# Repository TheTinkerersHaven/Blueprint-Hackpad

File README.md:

Repo containing the files for my HackPad made for Blueprint by Hack Club & AMD.
---
BOM:
- 1x Seeed Studio XIAO RP2040
- 1x 128x64 0.91" I2C OLED Screen
- 2x ALPS EC11 Rotary Encoders
- 5x Cherry MX-Style Mechanical Key Switches
- 8x M3 threaded inserts (the holes are 4.7mm diameter and 4mm deep)
- 8x M3 Screws
---
Images:

---
NOTE: the case's USB-C hole is taller than usual, to allow the XIAO to be mounted either as SMD or THT.

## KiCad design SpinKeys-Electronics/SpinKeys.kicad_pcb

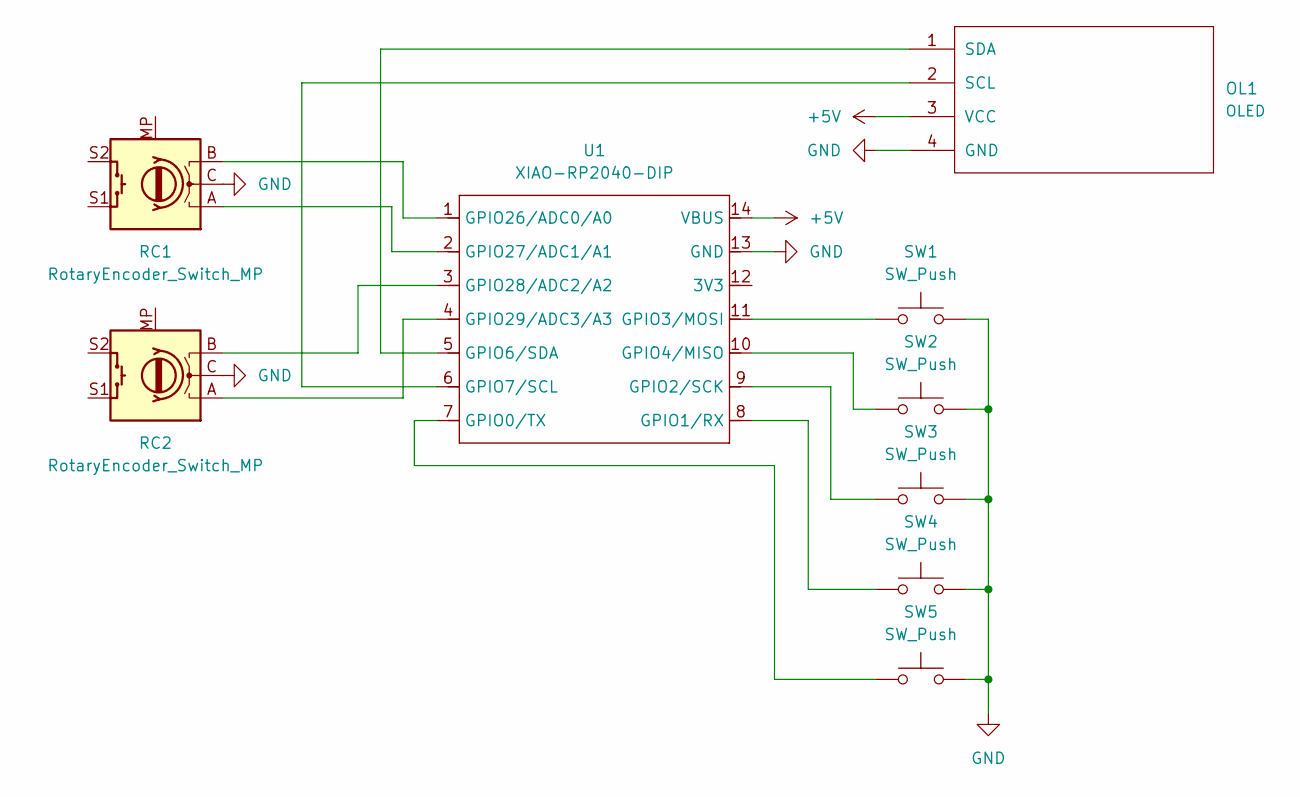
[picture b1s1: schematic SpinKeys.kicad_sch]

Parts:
OL1: OLED; SSD1306-0.91-OLED-4pin-128x32
RC1, RC2: RotaryEncoder_Switch_MP; RotaryEncoder_Alps_EC11E-Switch_Vertical_H20mm_CircularMoun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
SW1, SW2, SW3, SW4, SW5: SW_Push; SW_Cherry_MX_1.00u_PCB
U1: XIAO-RP2040-DIP

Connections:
+5V: OL1.3 (VCC), U1.14 (VBUS)
GND: OL1.4 (GND), RC1.C, RC2.C, SW1.2, SW2.2, SW3.2, SW4.2, SW5.2, U1.13 (GND)
unnamed: OL1.2 (SCL), U1.6 (GPIO7/SCL)
unnamed: OL1.1 (SDA), U1.5 (GPIO6/SDA)
unnamed: SW5.1, U1.7 (GPIO0/TX)
unnamed: SW4.1, U1.8 (GPIO1/RX)
unnamed: SW3.1, U1.9 (GPIO2/SCK)
unnamed: SW1.1, U1.11 (GPIO3/MOSI)
unnamed: SW2.1, U1.10 (GPIO4/MISO)
unnamed: RC1.B, U1.1 (GPIO26/ADC0/A0)
unnamed: RC1.A, U1.2 (GPIO27/ADC1/A1)
unnamed: RC2.B, U1.3 (GPIO28/ADC2/A2)
unnamed: RC2.A, U1.4 (GPIO29/ADC3/A3)

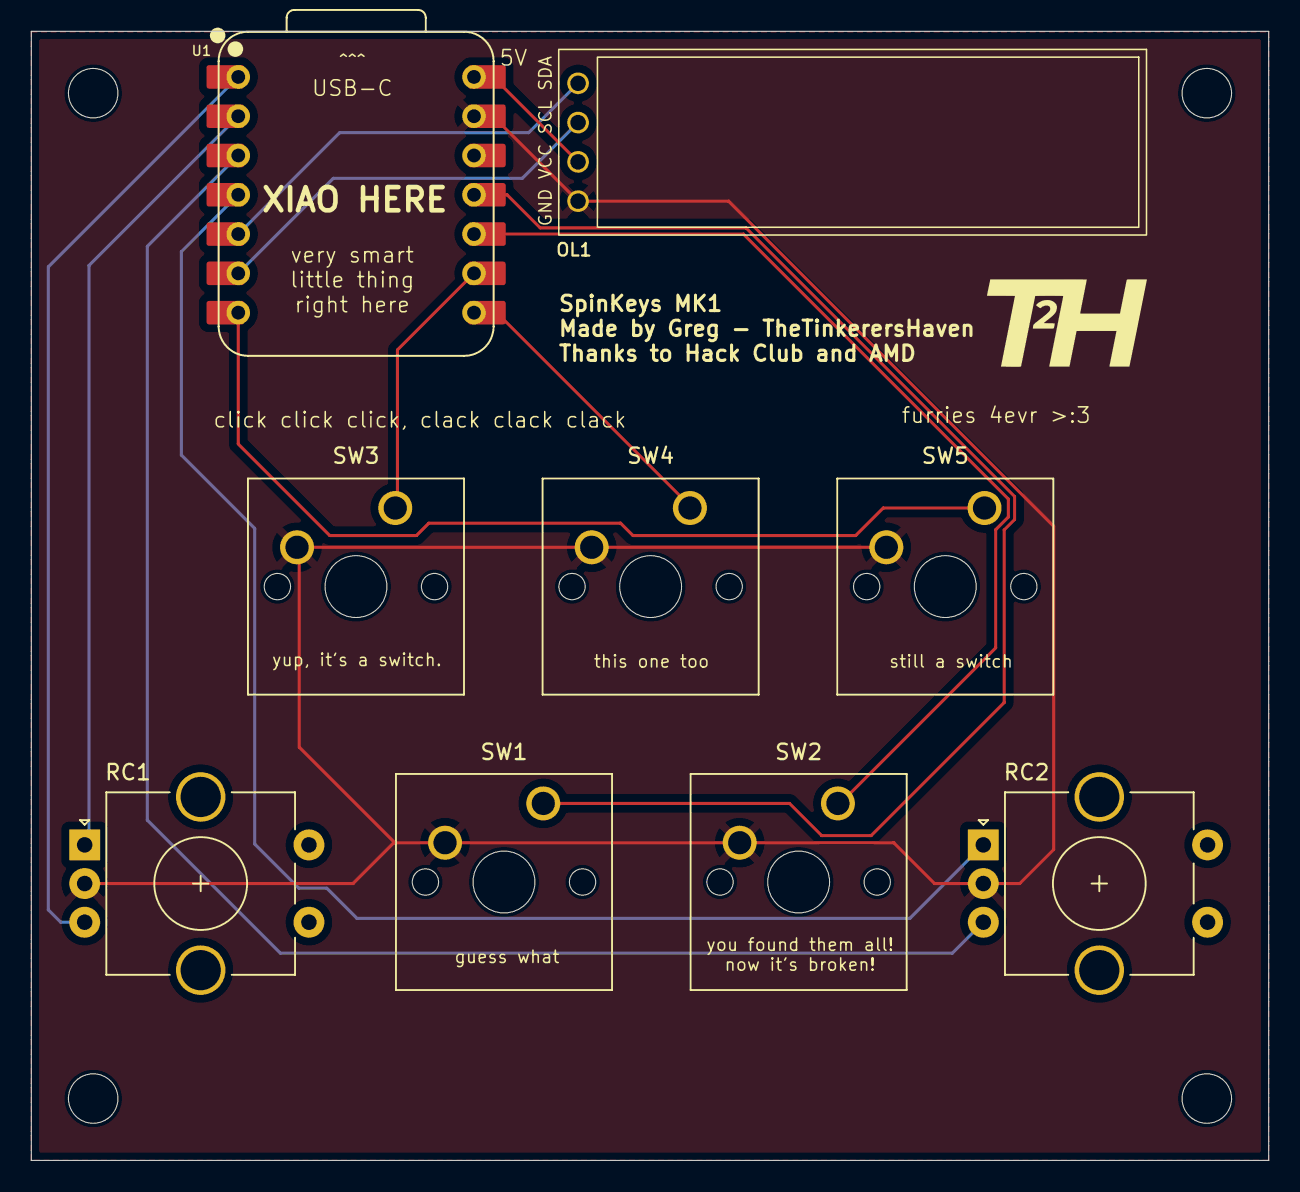
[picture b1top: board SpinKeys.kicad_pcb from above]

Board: 2 copper layers, 80.0 x 73.0 mm, 9 parts (0 on the bottom side), 13 nets.

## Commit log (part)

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2025-12-06 First upload
2025-12-06 The board is done!
2025-12-06 Initialize README with project details and images
    Added introductory information and images to README.
2025-12-06 Small changes in naming
2025-12-06 Added used libraries and renamed project
    CAUTION: I do not own the libraries used.
2025-12-06 remove backups
2025-12-07 Fixed some references and made the PCB step file better
2025-12-16 Update PCB layout and silkscreen for SpinKeys MK1
2025-12-21 Upload STEP files, update PCB to final
2025-12-21 Remade README to comply with requirements
    Added bill of materials and required images.
2025-12-23 Added individual case CAD model photos
2025-12-27 Fixed a schematic-pcb link, added fab files
